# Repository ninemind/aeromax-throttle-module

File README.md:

# DIY Throttle Module for the VIRPIL CDT-AEROMAX

An unofficial, community-built throttle module for the VIRPIL CDT-AEROMAX. This project began as a working replacement for the unavailable factory throttle module, but the interface can support much more than the original-style lever.

The design combines 3D-printed mechanical parts, a custom KiCad sensor PCB, and a magnetic position sensor. The module interface also provides a connection for an additional button, leaving room for custom levers, collectives, twin-throttle designs, and other original controls.

## Print files and profiles

For ready-to-print files, tested print profiles, photos, and the illustrated assembly guide, see the [MakerWorld project page](https://makerworld.com/en/models/3148591-virpil-aeromax-throttle-module#profileId-3556232). This repository is the canonical source for the editable CAD, KiCad design, and PCB manufacturing files.

## What is here

| Folder or file | Contents |
| --- | --- |
| `Aeromax_Throttle_Module.3mf` | Printable mechanical model and print setup |
| `assembly.pdf` | Illustrated mechanical assembly guide |
| `Aeromax_Throttle_Module.step` | Neutral CAD exchange model for viewing and remixing |
| `images/` | Project renderings used in this README |
| `kikad/` | Editable KiCad schematic, PCB, and project files |
| `manufacturing/v1.0/` | Tested v1.0 Gerbers and JLCPCB assembly files |

## Build overview

Start with [the illustrated assembly guide](assembly.pdf). It covers the required parts and the complete mechanical assembly sequence.

The PCB is a separate build step. The editable source is in [`kikad/`](kikad/); users who want JLCPCB assembly should use the files in [`manufacturing/v1.0/`](manufacturing/v1.0/).

## Ordering the PCB

For the v1.0 PCB:

1. Upload [`Aeromax_Throttle_Module_Gerbers_v1.0.zip`](manufacturing/v1.0/Aeromax_Throttle_Module_Gerbers_v1.0.zip) to JLCPCB to order bare PCBs.
2. For PCBA, upload [`Aeromax_Throttle_Module_JLCPCB_BOM_v1.0.csv`](manufacturing/v1.0/Aeromax_Throttle_Module_JLCPCB_BOM_v1.0.csv) and [`Aeromax_Throttle_Module_JLCPCB_CPL_v1.0.csv`](manufacturing/v1.0/Aeromax_Throttle_Module_JLCPCB_CPL_v1.0.csv) during the assembly order.
3. Review component availability, placements, rotation, and the JLCPCB preview before paying.

`Aeromax_Throttle_Module_KiCad_BOM_v1.0.csv` and `Aeromax_Throttle_Module_Position_Export_v1.0.csv` are KiCad exports retained for reference. The JLCPCB-specific BOM and CPL are the files intended for JLCPCB assembly.

## Ideas for remixes

This design does not have to look like the original throttle module. Possible adaptations include:

- A longer or shorter lever with a custom grip
- A collective-style control
- Twin levers or a different axis arrangement
- A lever with an integrated button using the module's additional button connection
- A completely new enclosure or mounting approach

If you make a variant, please share photos, source files, and notes that will help the next builder.

## Support

If this project was useful and you would like to support future designs:

## Important

This is an unofficial community project. It is not affiliated with, endorsed by, or supported by VIRPIL Controls. Verify fitment, wiring, and safe operation before installation. You build and use this project at your own risk.

## License

Copyright (c) 2026 ninemind. This project is licensed under the [CERN Open Hardware Licence Version 2 - Strongly Reciprocal](LICENSE) (`CERN-OHL-S-2.0`). You may use, make, modify, and distribute the design and products based on it, provided that distributed modifications remain available under the same licence.

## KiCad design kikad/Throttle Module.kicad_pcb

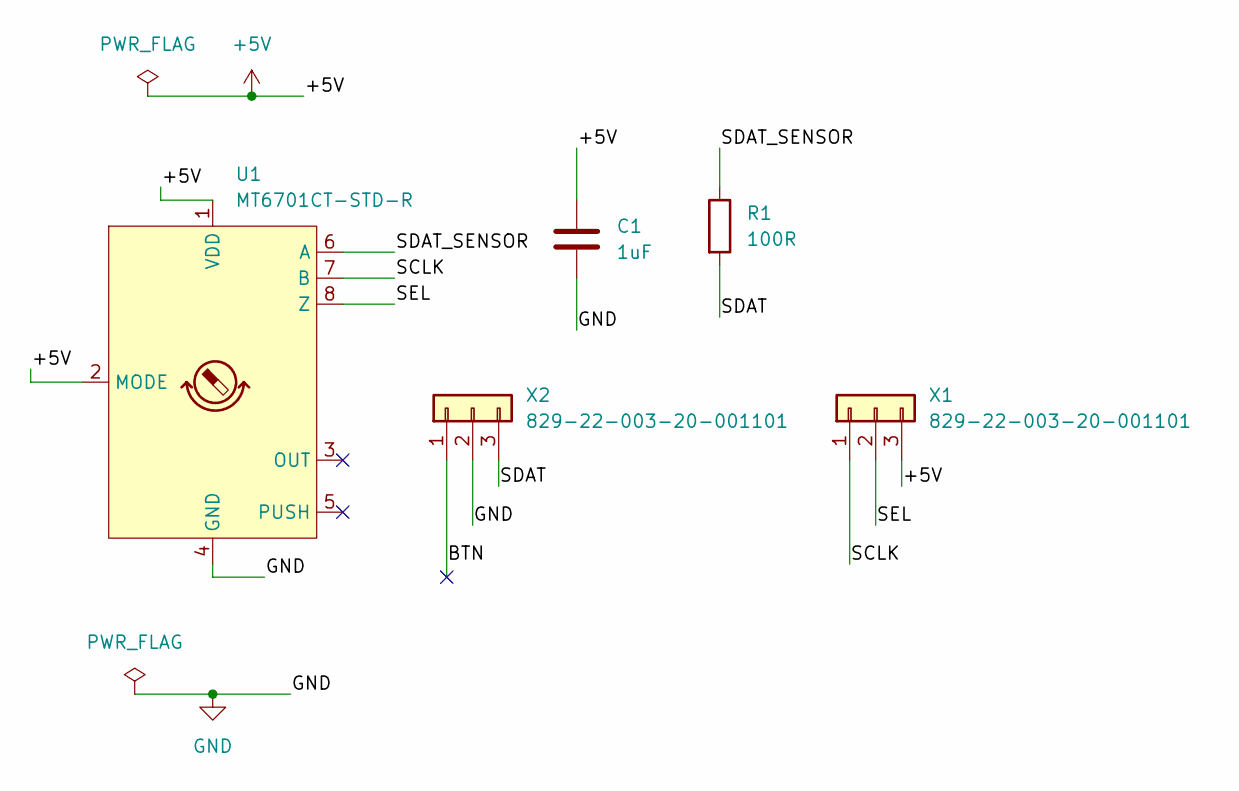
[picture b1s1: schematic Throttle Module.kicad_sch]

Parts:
C1: 1uF; C_0603_1608Metric; Voltage 16V
R1: 100R; R_0603_1608Metric; Tolerance 1%
U1: MT6701CT-STD-R; SO-8_3.9x4.9mm_P1.27mm; MPN MT6701CT-STD-R
X1, X2: 829-22-003-20-001101; MILL-MAX_829-22-003-20-001101

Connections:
+5V: C1.1, U1.1 (VDD), U1.2 (MODE), X1.3
/BTN: X2.1
/SCLK: U1.7 (B), X1.1
/SDAT: R1.2, X2.3
/SDAT_SENSOR: R1.1, U1.6 (A)
/SEL: U1.8 (Z), X1.2
GND: C1.2, U1.4 (GND), X2.2

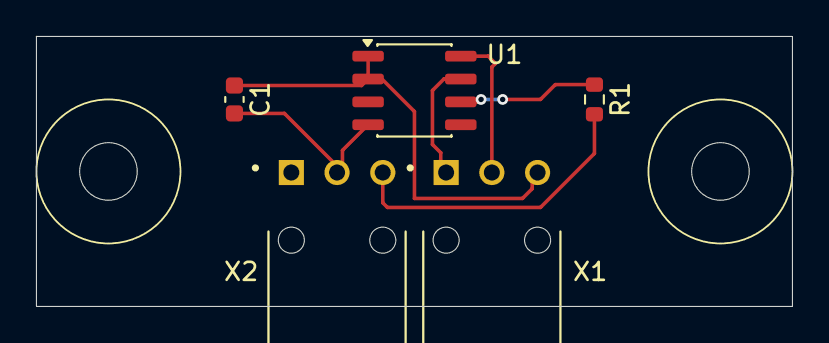
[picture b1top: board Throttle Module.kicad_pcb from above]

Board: 2 copper layers, 42.0 x 15.0 mm, 5 parts (0 on the bottom side), 6 nets.

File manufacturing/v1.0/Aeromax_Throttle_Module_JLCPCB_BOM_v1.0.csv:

Comment,Designator,Footprint,LCSC Part #
1uF 0603 X7R 10V+,C1,C_0603_1608Metric,
100R 0603 1%,R1,R_0603_1608Metric,
MT6701CT-STD-R,U1,SO-8_3.9x4.9mm_P1.27mm,C2856764
829-22-003-20-001101,"X1,X2",MILL-MAX_829-22-003-20-001101,
